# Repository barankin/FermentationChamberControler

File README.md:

# Fermentation Chamber Controller
arduino based fermentation chamber temperature controller

* Stage one including:
 * Arduino Nano
 * 1602 LCD display
 * Rotary encoder for changing temperature
 * Two temperature probes DS18B20 using one wire bus
 * Relay for turning compressor on and off
 * Relay for turning heater on and off
* Stage two including:
 * Logging using ESP-01 and Ai Thinker commands over hardware serial
* Stage three including:
 * Full control and status via ESP-01

# Background
* The LCD circuit for the LCD HelloWorld. We will use the same pin configuration:
 * LCD RS pin to digital pin 12
 * LCD Enable pin to digital pin 11
 * LCD D4 pin to digital pin 5
 * LCD D5 pin to digital pin 4
 * LCD D6 pin to digital pin 3
 * LCD D7 pin to digital pin 2
 * LCD R/W pin to ground
 * LCD VSS pin to ground
 * LCD VCC pin to 5V
 * 10K resistor:
 * ends to +5V and ground
 * wiper to LCD VO pin (pin 3)

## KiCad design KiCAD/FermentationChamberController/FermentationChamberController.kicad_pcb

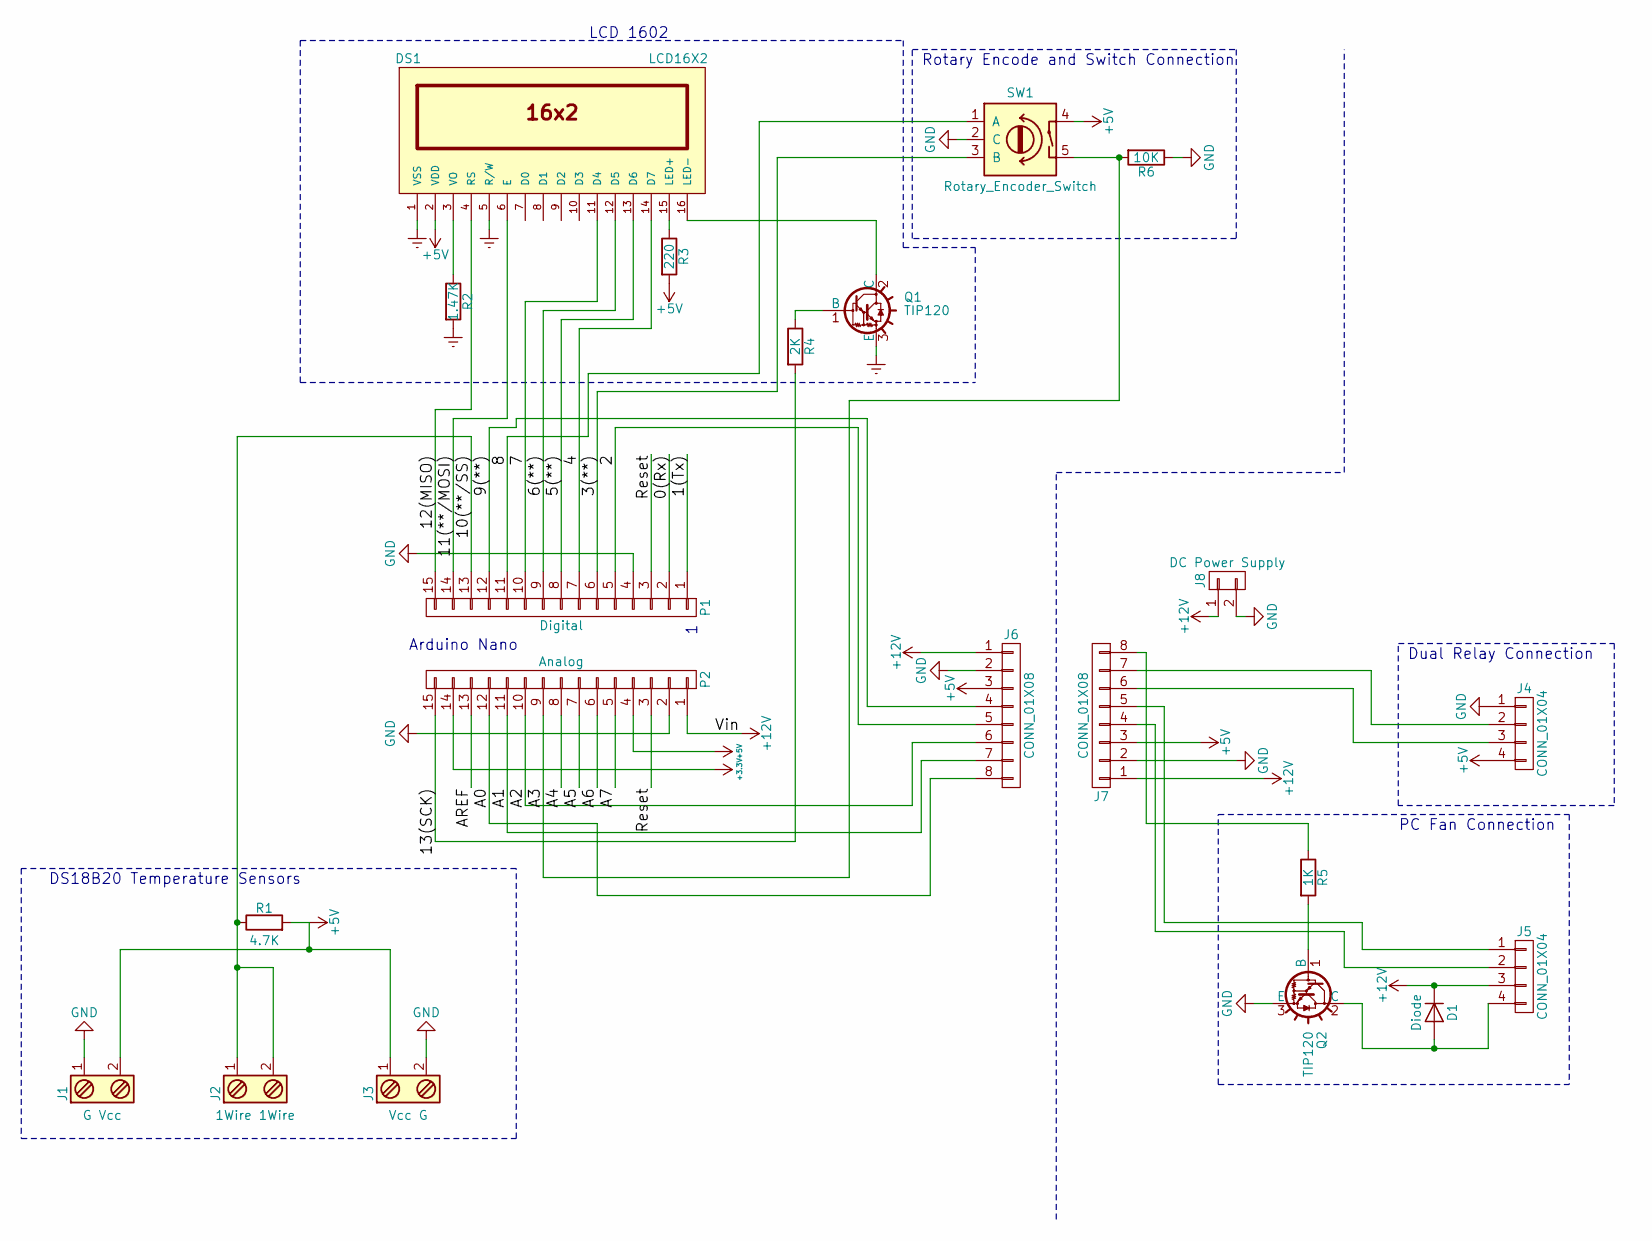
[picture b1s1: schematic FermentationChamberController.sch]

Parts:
D1: Diode; D_DO-15_P10.16mm_Horizontal
DS1: LCD16X2; Pin_Header_Straight_1x16_Pitch2.54mm
J1: G Vcc; bornier2
J2: 1Wire 1Wire; bornier2
J3: Vcc G; bornier2
J4, J5: CONN_01X04; Pin_Header_Straight_1x04_Pitch2.54mm
J6, J7: CONN_01X08; RJ45_8
J8: DC Power Supply; Pin_Header_Straight_1x02_Pitch1.27mm
P1: Digital; Pin_Header_Straight_1x15_Pitch2.54mm
P2: Analog; Pin_Header_Straight_1x15_Pitch2.54mm
Q1: TIP120; TO-220_Horizontal
Q2: TIP120; TO-220_Vertical
R1: 4.7K; R_Axial_DIN0207_L6.3mm_D2.5mm_P10.16mm_Horizontal
R2: 1.47K; R_Axial_DIN0207_L6.3mm_D2.5mm_P10.16mm_Horizontal
R3: 220; R_Axial_DIN0207_L6.3mm_D2.5mm_P10.16mm_Horizontal
R4: 2K; R_Axial_DIN0207_L6.3mm_D2.5mm_P10.16mm_Horizontal
R5: 1K; R_Axial_DIN0207_L6.3mm_D2.5mm_P10.16mm_Horizontal
R6: 10K; R_Axial_DIN0207_L6.3mm_D2.5mm_P10.16mm_Horizontal
SW1: Rotary_Encoder_Switch; Pin_Header_Straight_1x05_Pitch2.54mm

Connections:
+3V3: P2.14
+5V: DS1.2 (VDD), J1.2, J3.1, J4.4, J6.3, J7.3, P2.4, R1.2, R3.2, SW1.4
+12V: D1.1 (K), J5.3, J6.1, J7.1, J8.1, P2.1
/0(Rx): P1.2
/1(Tx): P1.1
/2: J6.5, P1.5
/3(**): P1.6, SW1.3 (B)
/4: DS1.14 (D7), P1.7
/5(**): DS1.13 (D6), P1.8
/6(**): DS1.12 (D5), P1.9
/7: DS1.11 (D4), P1.10
/8: P1.11, SW1.1 (A)
/9(**): J6.4, P1.12
/10(**/SS): J2.1, J2.2, P1.13, R1.1
/11(**/MOSI): DS1.6 (E), P1.14
/12(MISO): DS1.4 (RS), P1.15
/13(SCK): P2.15, R4.2
/A0: J6.8, P2.12
/A1: J6.7, P2.11
/A2: J6.6, P2.10
/A3: P2.9, R6.2, SW1.5
/A4: P2.8
/A5: P2.7
/A6: P2.6
/A7: P2.5
/AREF: P2.13
/Reset: P1.3, P2.3
Earth: DS1.1 (VSS), DS1.5 (R/W), Q1.3 (E), R2.2
GND: J1.1, J3.2, J4.1, J6.2, J7.2, J8.2, P1.4, P2.2, Q2.3 (E), R6.1, SW1.2 (C)
unnamed: D1.2 (A), J5.4, Q2.2 (C)
unnamed: DS1.3 (VO), R2.1
unnamed: DS1.15 (LED+), R3.1
unnamed: DS1.16 (LED-), Q1.2 (C)
unnamed: J4.2, J7.7
unnamed: J4.3, J7.6
unnamed: J5.1, J7.5
unnamed: J5.2, J7.4
unnamed: J7.8, R5.1
unnamed: Q1.1 (B), R4.1
unnamed: Q2.1 (B), R5.2

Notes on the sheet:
LCD 1602
DS18B20 Temperature Sensors
PC Fan Connection
Dual Relay Connection
Rotary Encode and Switch Connection
Arduino Nano

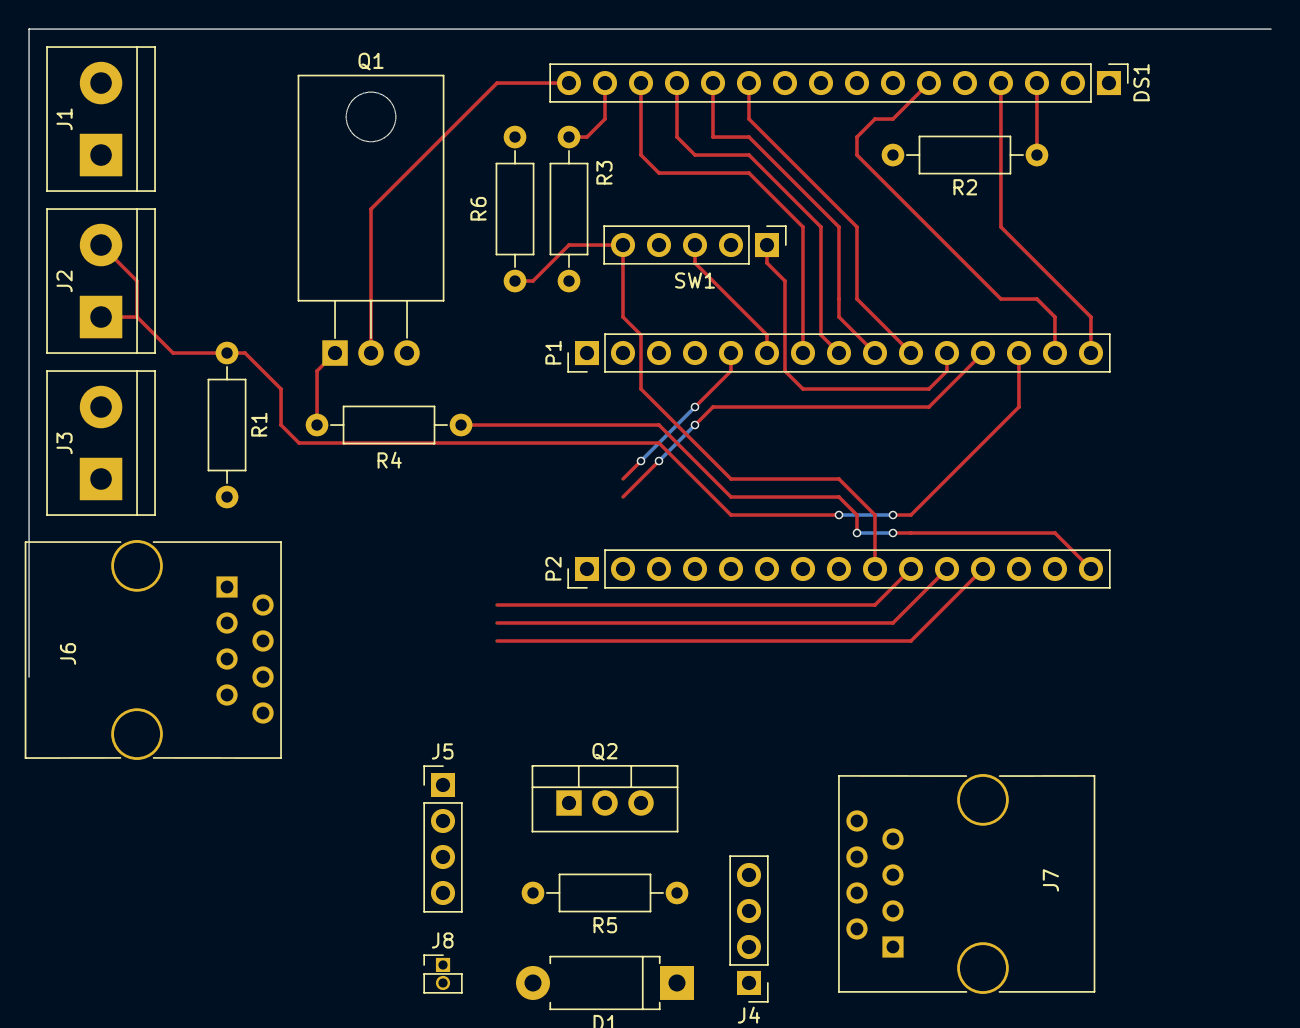
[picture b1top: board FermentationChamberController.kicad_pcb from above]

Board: 2 copper layers, 21 parts (0 on the bottom side), 32 nets.

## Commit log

2017-02-08 Added main file for working
2017-02-08 Corrected spelling
2017-02-09 Started building the loop. Added temperature detection every 5 seconds.
2017-02-09 Now making sure it builds before uploading
2017-02-09 Preliminary implementation of fan code
2017-02-09 Minor refinement to fan interval
2017-02-10 Applying markdown formatting to README
    Syntax taken from
    https://daringfireball.net/projects/markdown/syntax
2017-03-12 Adding Fritzing File
    Added a WIP fritzing file
2017-03-17 Add Fritzing File
2017-03-19 Updated Rotatry encode and Fan
    Updated based on testing done with rotary encode and fan speed for a 4 wire fan (PWM controlled).
2017-03-31 <updated fritzing file, almost done
    definitely more organized so far
2017-03-31 Improving Fritzign file
    Getting it more complete and better organized visually.
2017-04-22 Progress
    added rotary encode switch
2017-04-22 Added diod to fan control drawing
2017-05-05 Started to add test programs
2017-05-06 Updated rotary encoder wiring
2017-05-06 Updated LCD wiring
    Changed power from VCC to pin 13 so that the display can be turned on and off.
2017-05-06 Added TIP120 to switch on LCD
2017-05-06 modified TIP120 to only swith LCD backlight
2017-05-16 Created KiCAD File and began schematic with the Arduino and LCD 1602 circuit.
2017-05-16 Minor updates to lcd schematic
2017-05-17 Added test suites
    Test sutie for one wire bus and temperature measurement
2017-05-17 Basic schematic complete per Fritzing file
2017-05-17 Minor schematic fixes (fan diode)
2017-05-17 And another correction to the diode
2017-05-17 Annotated
2017-05-17 Created KiCAD netlist
2017-05-18 Workign on the PCB Layout, first step.
2017-05-18 Updated header styles for the arduino, fan and relay connectors.
2017-05-18 Updated readme to state arduino nano
    Arduino Uno board is used in the Fritzing file but the actual build will use a Nano.
2017-05-19 Updated PCB layour
    almost done.... maybe
2017-05-26 Updated schematic to split into two pcbs
2017-06-09 Updates to Kicad and testing
    RJ 45 connectors
    bad test for wifi...
2017-08-06 Added Fan Test
2017-08-06 Temp test updates and corrections
    Trouble shooting circuit
2017-08-06 FanTest update to speed command
2017-08-27 Fan working (except rpm measure)
2017-09-04 wifitest2
    crashing on tcp connection
2017-09-04 wifiupload working
    Apparently i was running out of memory. 1k is too large a buffer to receive the web data! commented out all receipt of web data
2017-10-09 RelayTest Added
2017-10-09 Fixed relay to be normally open
    Originally, I was starting the heater and compressor automatically. Now, they are always off unless turned on.... much better
2017-10-09 Starting Main Program from Scratch
    Moved original file to "superseded" folder.
2018-10-01 Updated to Nano and testing Git Gui again
